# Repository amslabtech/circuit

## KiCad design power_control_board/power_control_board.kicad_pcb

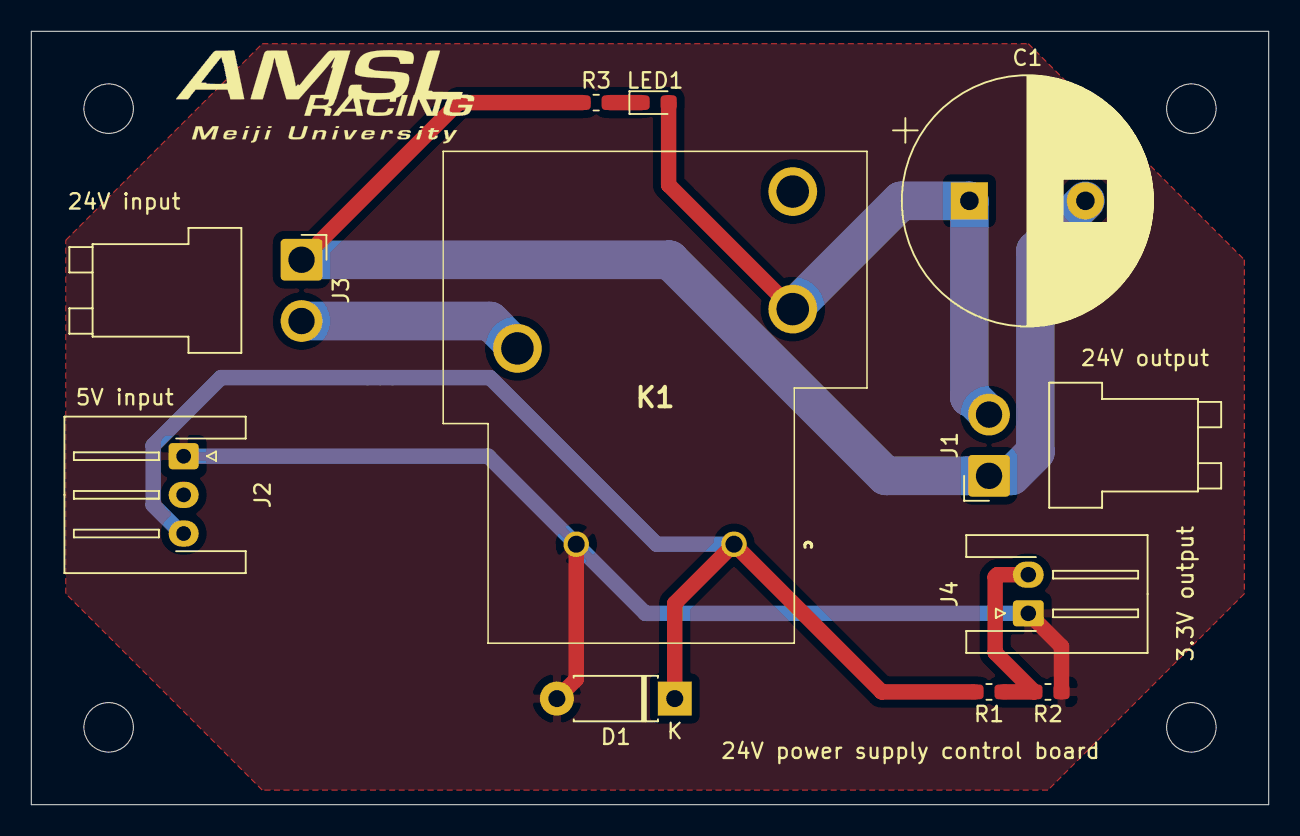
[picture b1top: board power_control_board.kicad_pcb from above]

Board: 2 copper layers, 80.0 x 50.0 mm, 11 parts (0 on the bottom side), 7 nets.

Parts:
C1: 2200u; CP_Radial_D16.0mm_P7.50mm
D1: D; D_DO-41_SOD81_P7.62mm_Horizontal
J1, J3: Conn_01x02; JST_VH_B2PS-VH_1x02_P3.96mm_Horizontal
J2: Conn_01x03; JST_XH_S3B-XH-A-1_1x03_P2.50mm_Horizontal
J4: Conn_01x02; JST_XH_S2B-XH-A-1_1x02_P2.50mm_Horizontal
K1: 953-1C-5DG-1; 9531C5DG1
LED1: LED; LED_0603_1608Metric_Pad1.05x0.95mm_HandSolder
R1, R3: 1k; R_0603_1608Metric_Pad1.05x0.95mm_HandSolder
R2: 2k; R_0603_1608Metric_Pad1.05x0.95mm_HandSolder

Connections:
+5V: D1.1, J2.3, K1.1, R1.2
+24V: J3.2, K1.5
GND: C1.2, J1.1, J3.1, R3.1
GNDD: D1.2, J2.1, J4.1, K1.2, R2.1
unnamed: C1.1, J1.2, K1.4, LED1.2
unnamed: J4.2, R1.1, R2.2
unnamed: LED1.1, R3.2

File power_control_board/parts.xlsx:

品名ヒンメイ | 型番カタバン | 個数コスウ | 単価タンカ | 合計ゴウケイ | 購入店コウニュウテン | 備考ビコウ
リレー | 953-1C-5DG-1 | 1 |  |  |  | digikeyの互換品？https://www.digikey.jp/product-detail/ja/panasonic-electric-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
VHコネクタ | VH2 | 2
XHコネクタ | XH3 | 1
電解コンデンサ(2200uF, 35V)デンカイ | UVK1V222MHD | 1
抵抗(1kΩ)テイコウ |  | 2
ダイオード | AX057 | 1

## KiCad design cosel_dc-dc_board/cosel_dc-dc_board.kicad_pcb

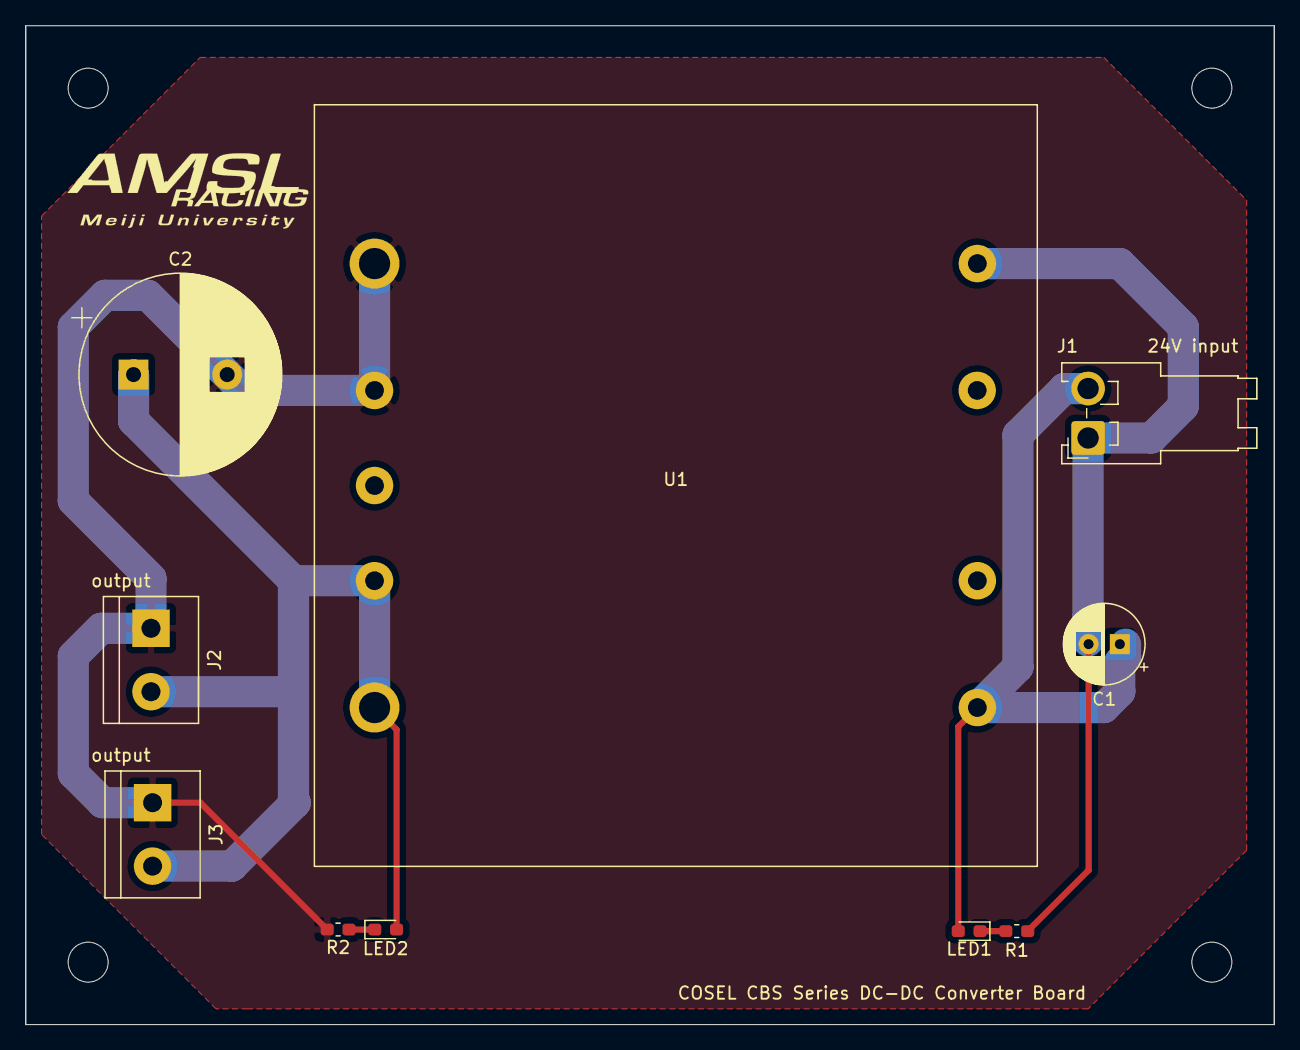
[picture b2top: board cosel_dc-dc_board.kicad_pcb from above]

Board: 2 copper layers, 100.0 x 80.0 mm, 10 parts (0 on the bottom side), 6 nets.

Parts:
C1: 100u; CP_Radial_D6.3mm_P2.50mm
C2: 1000u; CP_Radial_D16.0mm_P7.50mm
J1: Conn_01x02; JST_VH_S2P-VH_1x02_P3.96mm_Horizontal
J2, J3: Screw_Terminal_01x02; TerminalBlock_bornier-2_P5.08mm
LED1, LED2: LED; LED_0603_1608Metric_Pad1.05x0.95mm_HandSolder
R1, R2: 10k; R_0603_1608Metric_Pad1.05x0.95mm_HandSolder
U1: CBS

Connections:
+24V: C1.1, J1.2, LED1.2, U1.1
GND: C1.2, J1.1, R1.2, U1.4
GNDPWR: C2.2, J2.1, J3.1, R2.2, U1.8, U1.9
unnamed: C2.1, J2.2, J3.2, LED2.2, U1.5, U1.6
unnamed: LED1.1, R1.1
unnamed: LED2.1, R2.1

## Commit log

2019-05-02 add dc-dc board
